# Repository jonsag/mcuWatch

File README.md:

# mcuWatch

A watch based on an ATmega32P or an ESP8266 module with an RTC clock and a TFT screen  

## Links

### Arduino

[Tutorial on how to use DS3231 RTC Module](https://create.arduino.cc/projecthub/mdraber/tutorial-on-how-to-use-ds3231-rtc-module-e12b38)  
[The ST7735 TFT with arduino](https://www.electronics-lab.com/project/using-st7735-1-8-color-tft-display-arduino/)  
[Arduino DS3231 Real Time Clock With Color TFT](https://www.instructables.com/Arduino-DS3231-Real-time-clock-with-color-TFT/)  

### ESP8266

[ESP8266 pinout reference and how to use GPIO pins](https://microcontrollerslab.com/esp8266-pinout-reference-gpio-pins/)  
[ESP8266 Pinout Reference: Which GPIO pins should you use?](https://randomnerdtutorials.com/esp8266-pinout-reference-gpios/)  
[NodeMCU GPIO with Arduino IDE](https://www.electronicwings.com/nodemcu/nodemcu-gpio-with-arduino-ide)  

[Connecting a 1.77 inch TFT LCD screen to ESP8266](http://gogs.info/blog/2020/03/connecting-177-inch-TFT-LCD-screen-ESP8266/)  
[NodeMCU and 1.8" SPI ST7735 Display](https://www.instructables.com/NodeMCU-and-18-SPI-ST7735-Display/)  
[Interfacing ESP8266 NodeMCU with ST7735 TFT](https://simple-circuit.com/esp8266-nodemcu-st7735s-tft/)  
[ESP8266 NodeMCU Internet Clock with ST7735 TFT](https://simple-circuit.com/esp8266-nodemcu-st7735-tft-internet-clock/)  

### Libraries

[DS3231](https://github.com/NorthernWidget/DS3231)  
[Adafruit GFX Library](https://github.com/adafruit/Adafruit-GFX-Library)  
[Adafruit SSD1306](https://github.com/adafruit/Adafruit_SSD1306)  

#### Tiny/Compact TFT Graphics Library

[Tiny TFT Graphics Library](http://www.technoblogy.com/show?L6I)  

[Compact TFT Graphics Library](http://www.technoblogy.com/show?2LMJ)
[Source](https://github.com/technoblogy/compact-tft-graphics-library)

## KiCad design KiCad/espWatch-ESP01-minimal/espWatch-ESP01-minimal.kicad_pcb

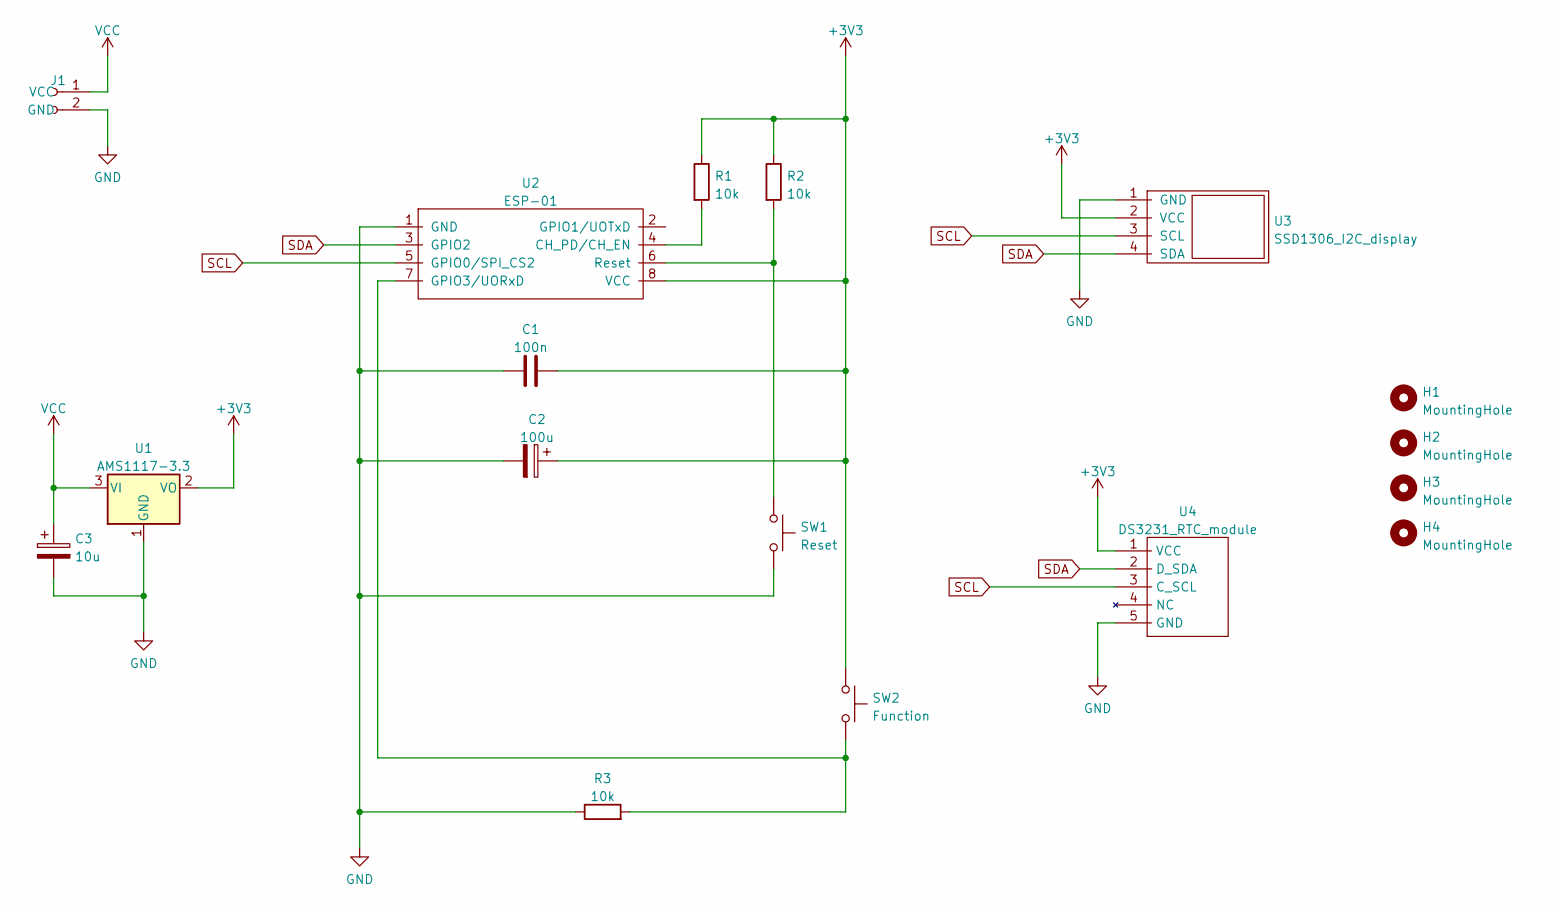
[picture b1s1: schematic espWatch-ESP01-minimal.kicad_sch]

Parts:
C1: 100n; C_Disc_D3.0mm_W1.6mm_P2.50mm_larg
C2: 100u; CP_Radial_D5.0mm_P2.00mm_larger
C3: 10u; CP_Radial_D5.0mm_P2.00mm_larger
H1, H2, H3, H4: MountingHole; MountingHole_3.2mm_M3
J1: 2-pin_power_input_header; 2-pin_power_input_header_larger_pads
R1, R2, R3: 10k; R_Axial_DIN0207_L6.3mm_D2.5mm_P10.16mm_Horizontal_larger_pa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
SW1: Reset; SW_PUSH_6mm_large
SW2: Function; SW_PUSH_6mm_large
U1: AMS1117-3.3; SOT-223-3_TabPin2
U2: ESP-01; ESP-01_w_pin_socket_large
U3: SSD1306_I2C_display; SSD1306_I2C_0.96_OLED_display_large
U4: DS3231_RTC_module; DS3231_RTC_module_large

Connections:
+3V3: C1.2, C2.1, R1.1, R2.1, SW2.1, U1.2 (VO), U2.8 (VCC), U3.2 (VCC), U4.1 (VCC)
GND: C1.1, C2.2, C3.2, J1.2 (GND), R3.1, SW1.2, U1.1 (GND), U2.1 (GND), U3.1 (GND), U4.5 (GND)
unnamed: R1.2, U2.4 (CH_PD/CH_EN)
unnamed: R2.2, SW1.1, U2.6 (Reset)
unnamed: R3.2, SW2.2, U2.7 (GPIO3/UORxD)
SCL: U2.5 (GPIO0/SPI_CS2), U3.3 (SCL), U4.3 (C_SCL)
SDA: U2.3 (GPIO2), U3.4 (SDA), U4.2 (D_SDA)
VCC: C3.1, J1.1 (VCC), U1.3 (VI)

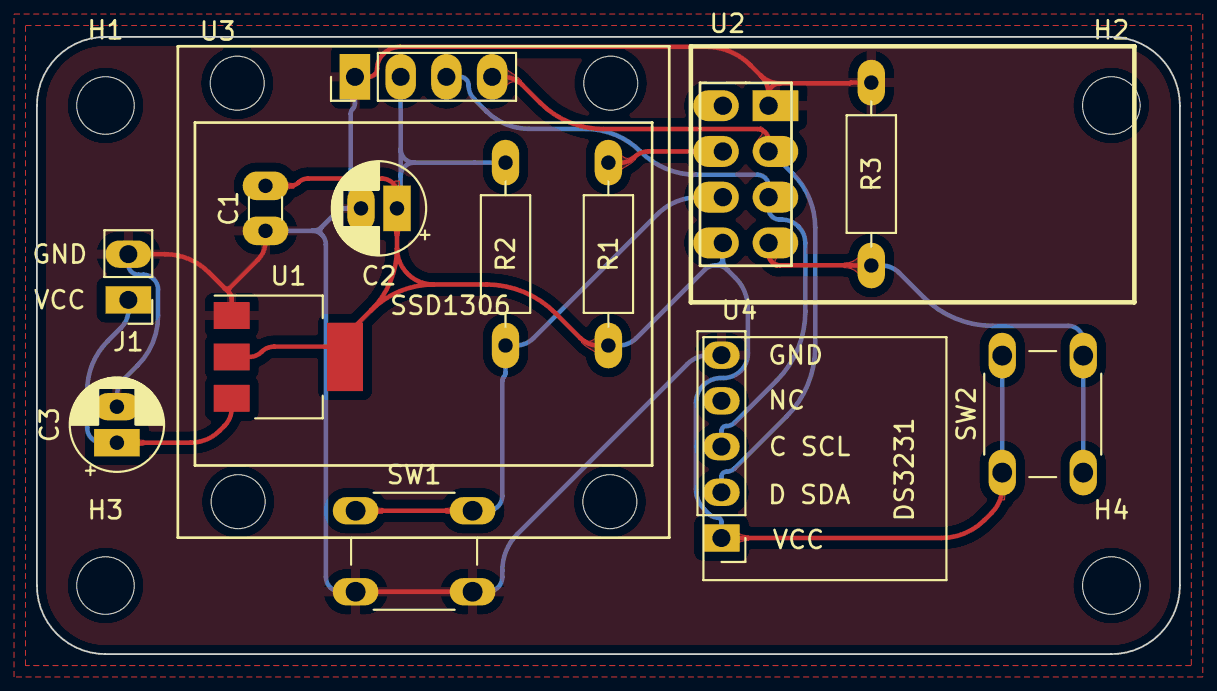
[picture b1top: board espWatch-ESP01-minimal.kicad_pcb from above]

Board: 2 copper layers, 63.5 x 34.3 mm, 17 parts (0 on the bottom side), 8 nets.

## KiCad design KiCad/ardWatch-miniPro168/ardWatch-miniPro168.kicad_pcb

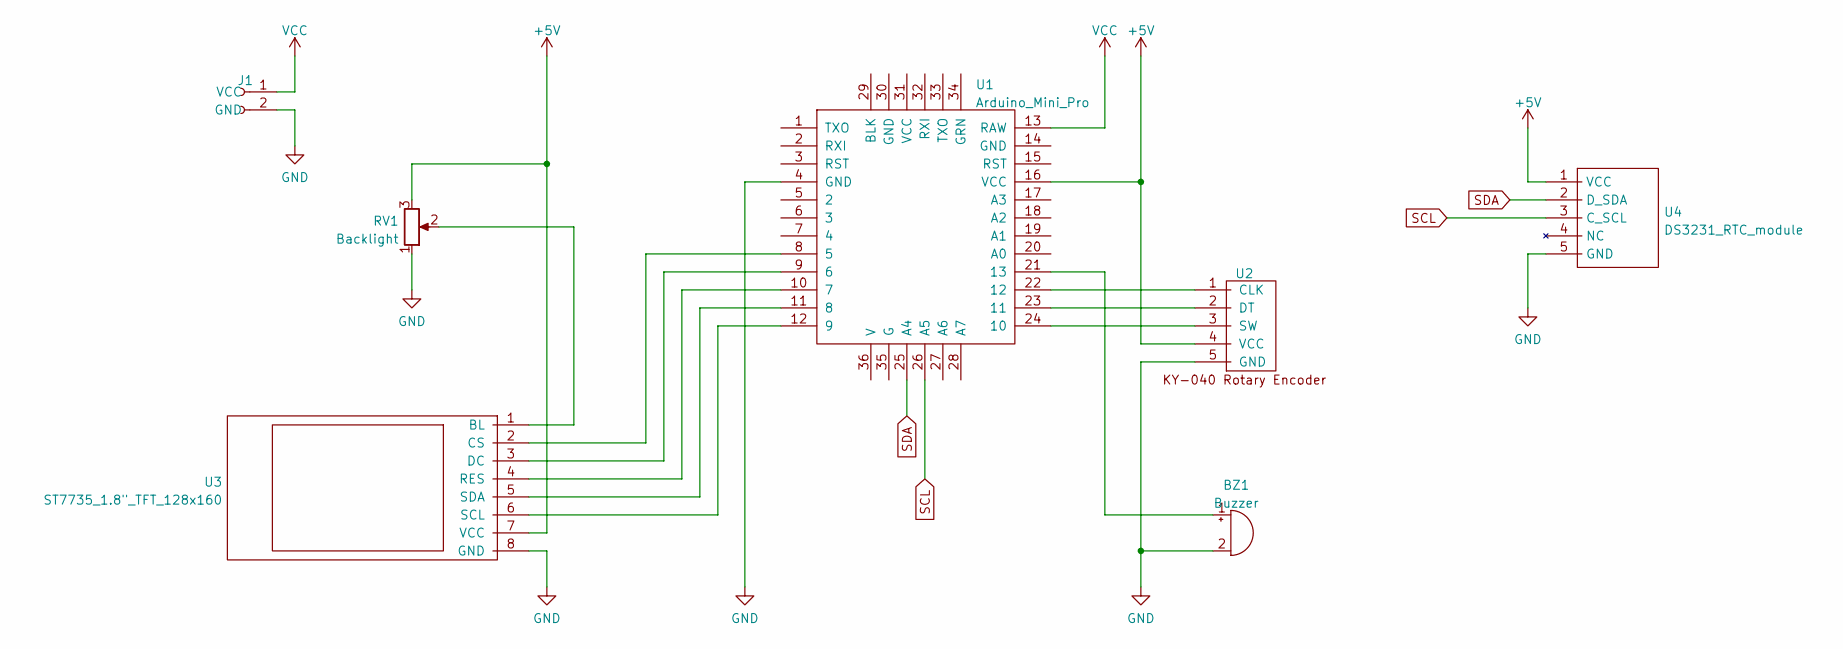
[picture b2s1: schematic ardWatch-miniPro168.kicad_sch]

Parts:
BZ1: Buzzer; Buzzer_TDK_PS1240P02BT_D12.2mm_H6.5mm_large
J1: 2-pin_power_input_header; 2-pin_power_input_header_larger_pads
RV1: Backlight; Potentiometer_Bourns_3339P_Vertical_large
U1: Arduino_Mini_Pro; Arduino_Pro_Mini_vC_larger_pads
U2: KY-040_Rotary_Encoder; KY-040_rotary_encoder module_w_header_large
U3: ST7735_1.8"_TFT_128x160; ST7735_1.8_TFT_display_128x160_large
U4: DS3231_RTC_module; DS3231_RTC_module_large

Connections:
+5V: RV1.3, U1.16 (VCC), U2.4 (VCC), U3.7 (VCC), U4.1 (VCC)
GND: BZ1.2 (+), J1.2 (GND), RV1.1, U1.4 (GND), U2.5 (GND), U3.8 (GND), U4.5 (GND)
unnamed: U1.8 (5), U3.2 (CS)
unnamed: U1.9 (6), U3.3 (DC)
unnamed: U1.10 (7), U3.4 (RES)
unnamed: U1.11 (8), U3.5 (SDA)
unnamed: U1.12 (9), U3.6 (SCL)
unnamed: BZ1.1 (-), U1.21 (13)
unnamed: U1.22 (12), U2.1 (CLK)
unnamed: U1.23 (11), U2.2 (DT)
unnamed: U1.24 (10), U2.3 (SW)
unnamed: RV1.2, U3.1 (BL)
SCL: U1.26 (A5), U4.3 (C_SCL)
SDA: U1.25 (A4), U4.2 (D_SDA)
VCC: J1.1 (VCC), U1.13 (RAW)

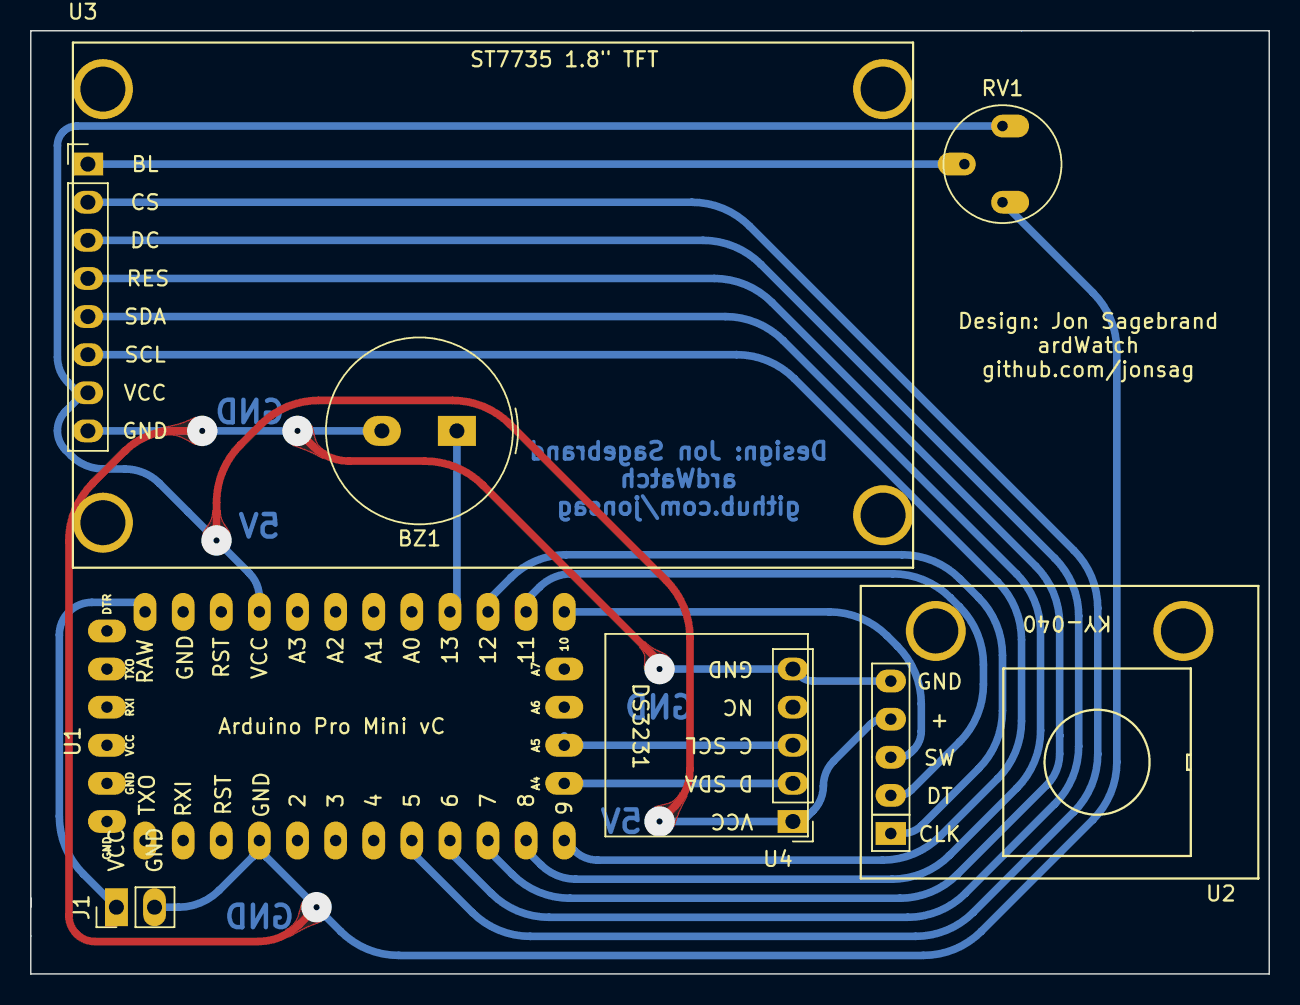
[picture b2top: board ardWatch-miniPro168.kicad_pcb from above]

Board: 2 copper layers, 82.5 x 62.9 mm, 7 parts (0 on the bottom side), 15 nets.

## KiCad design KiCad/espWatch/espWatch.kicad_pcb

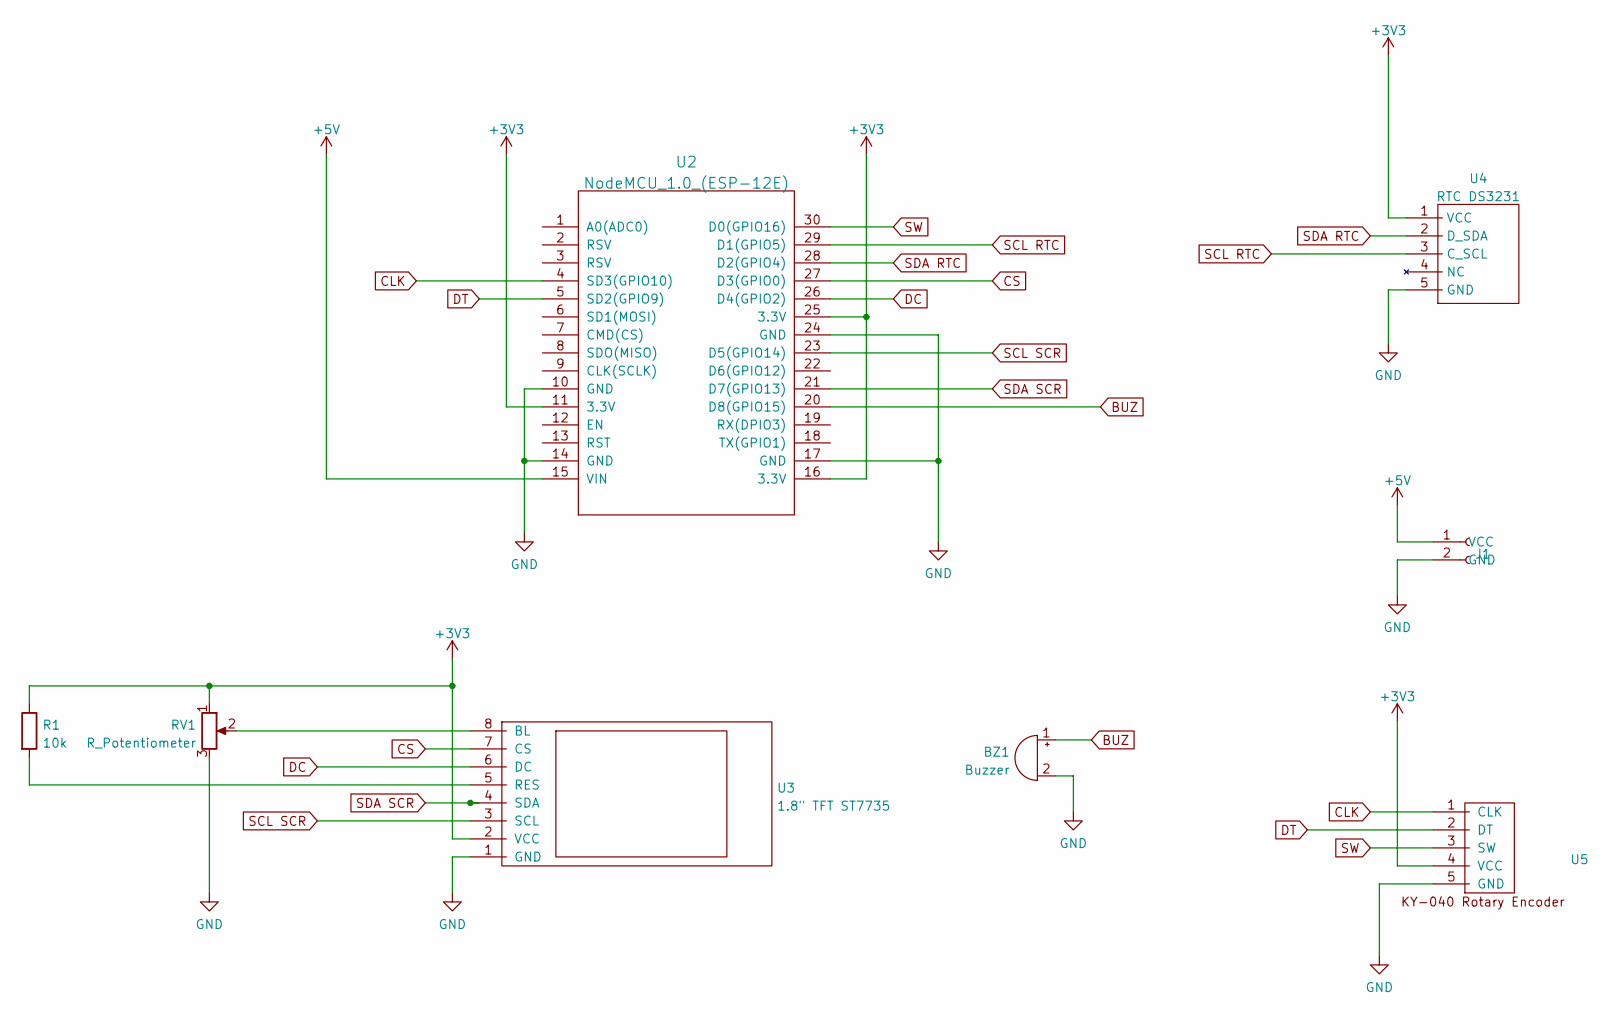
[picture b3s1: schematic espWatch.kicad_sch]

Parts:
BZ1: Buzzer; Buzzer_TDK_PS1240P02BT_D12.2mm_H6.5mm_large
J1: 2-pin_power_input_header; 2-pin_power_input_header_larger_pads
R1: 10k; R_Axial_DIN0207_L6.3mm_D2.5mm_P10.16mm_Horizontal_larger_pa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
RV1: R_Potentiometer; Potentiometer_Bourns_3339P_Vertical_large
U2: NodeMCU_1.0_(ESP-12E); NodeMCU-LoLinV3_w_pinsockets_large
U3: 1.8" TFT ST7735; ST7735_1.8_TFT_display_128x160_large
U4: RTC DS3231; DS3231_RTC_module_large
U5: KY-040_Rotary_Encoder; KY-040_rotary_encoder module_w_header_large

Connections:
+3V3: R1.1, RV1.1, U2.11 (3.3V), U2.16 (3.3V), U2.25 (3.3V), U3.2 (VCC), U4.1 (VCC), U5.4 (VCC)
+5V: J1.1 (VCC), U2.15 (VIN)
BUZ: BZ1.1 (-), U2.20 (D8(GPIO15))
CLK: U2.4 (SD3(GPIO10)), U5.1 (CLK)
CS: U2.27 (D3(GPIO0)), U3.7 (CS)
DC: U2.26 (D4(GPIO2)), U3.6 (DC)
DT: U2.5 (SD2(GPIO9)), U5.2 (DT)
GND: BZ1.2 (+), J1.2 (GND), RV1.3, U2.10 (GND), U2.14 (GND), U2.17 (GND), U2.24 (GND), U3.1 (GND), U4.5 (GND), U5.5 (GND)
unnamed: R1.2, U3.5 (RES)
unnamed: RV1.2, U3.8 (BL)
SCL RTC: U2.29 (D1(GPIO5)), U4.3 (C_SCL)
SCL SCR: U2.23 (D5(GPIO14)), U3.3 (SCL)
SDA RTC: U2.28 (D2(GPIO4)), U4.2 (D_SDA)
SDA SCR: U2.21 (D7(GPIO13)), U3.4 (SDA)
SW: U2.30 (D0(GPIO16)), U5.3 (SW)

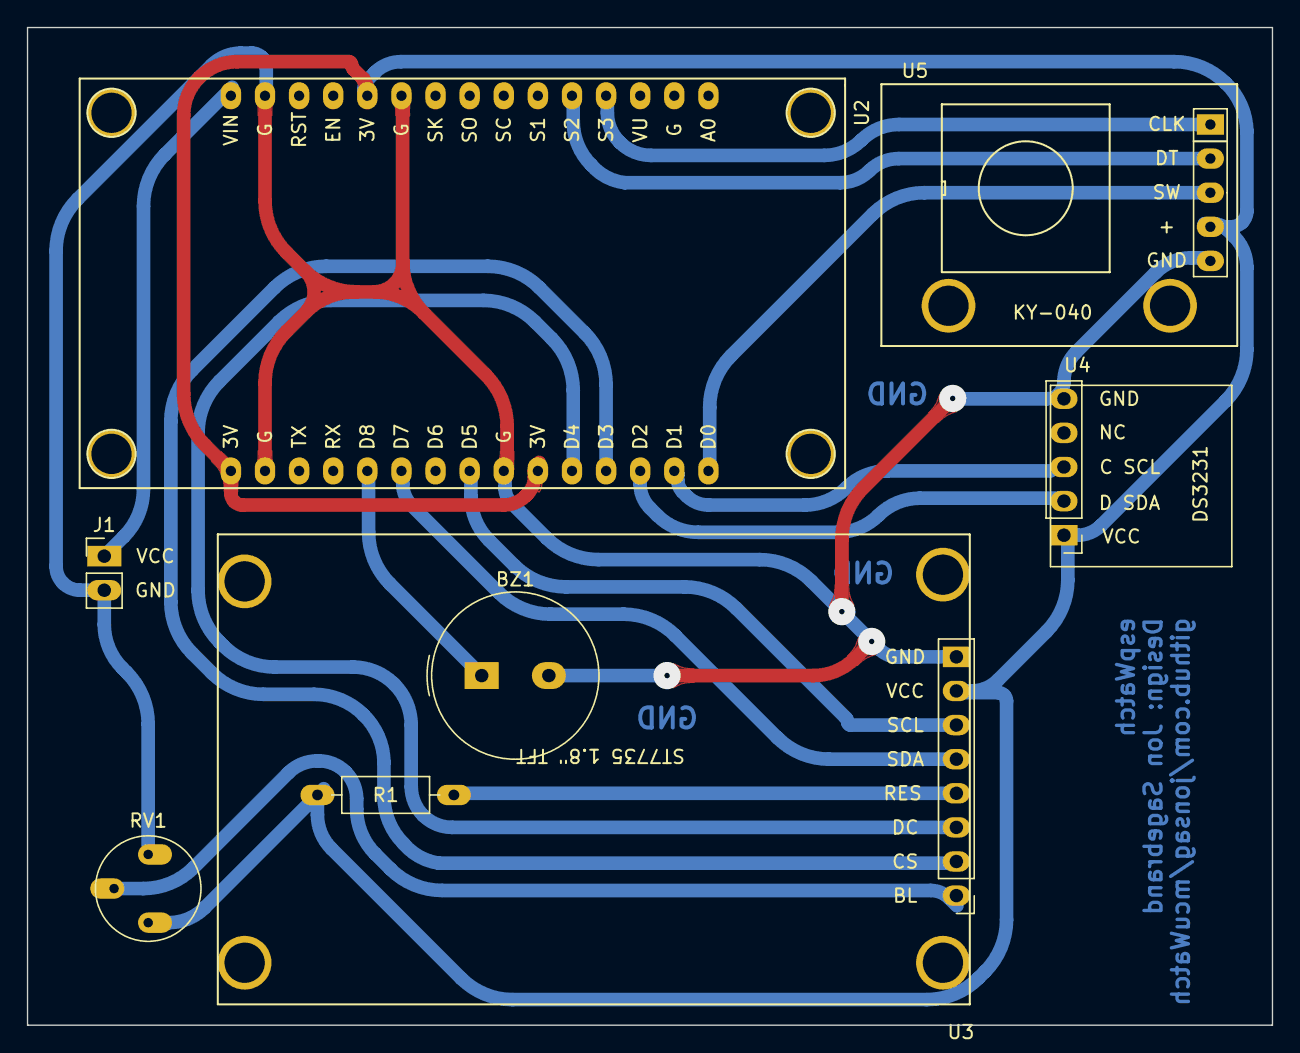
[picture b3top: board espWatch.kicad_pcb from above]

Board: 2 copper layers, 92.7 x 74.3 mm, 8 parts (0 on the bottom side), 15 nets.

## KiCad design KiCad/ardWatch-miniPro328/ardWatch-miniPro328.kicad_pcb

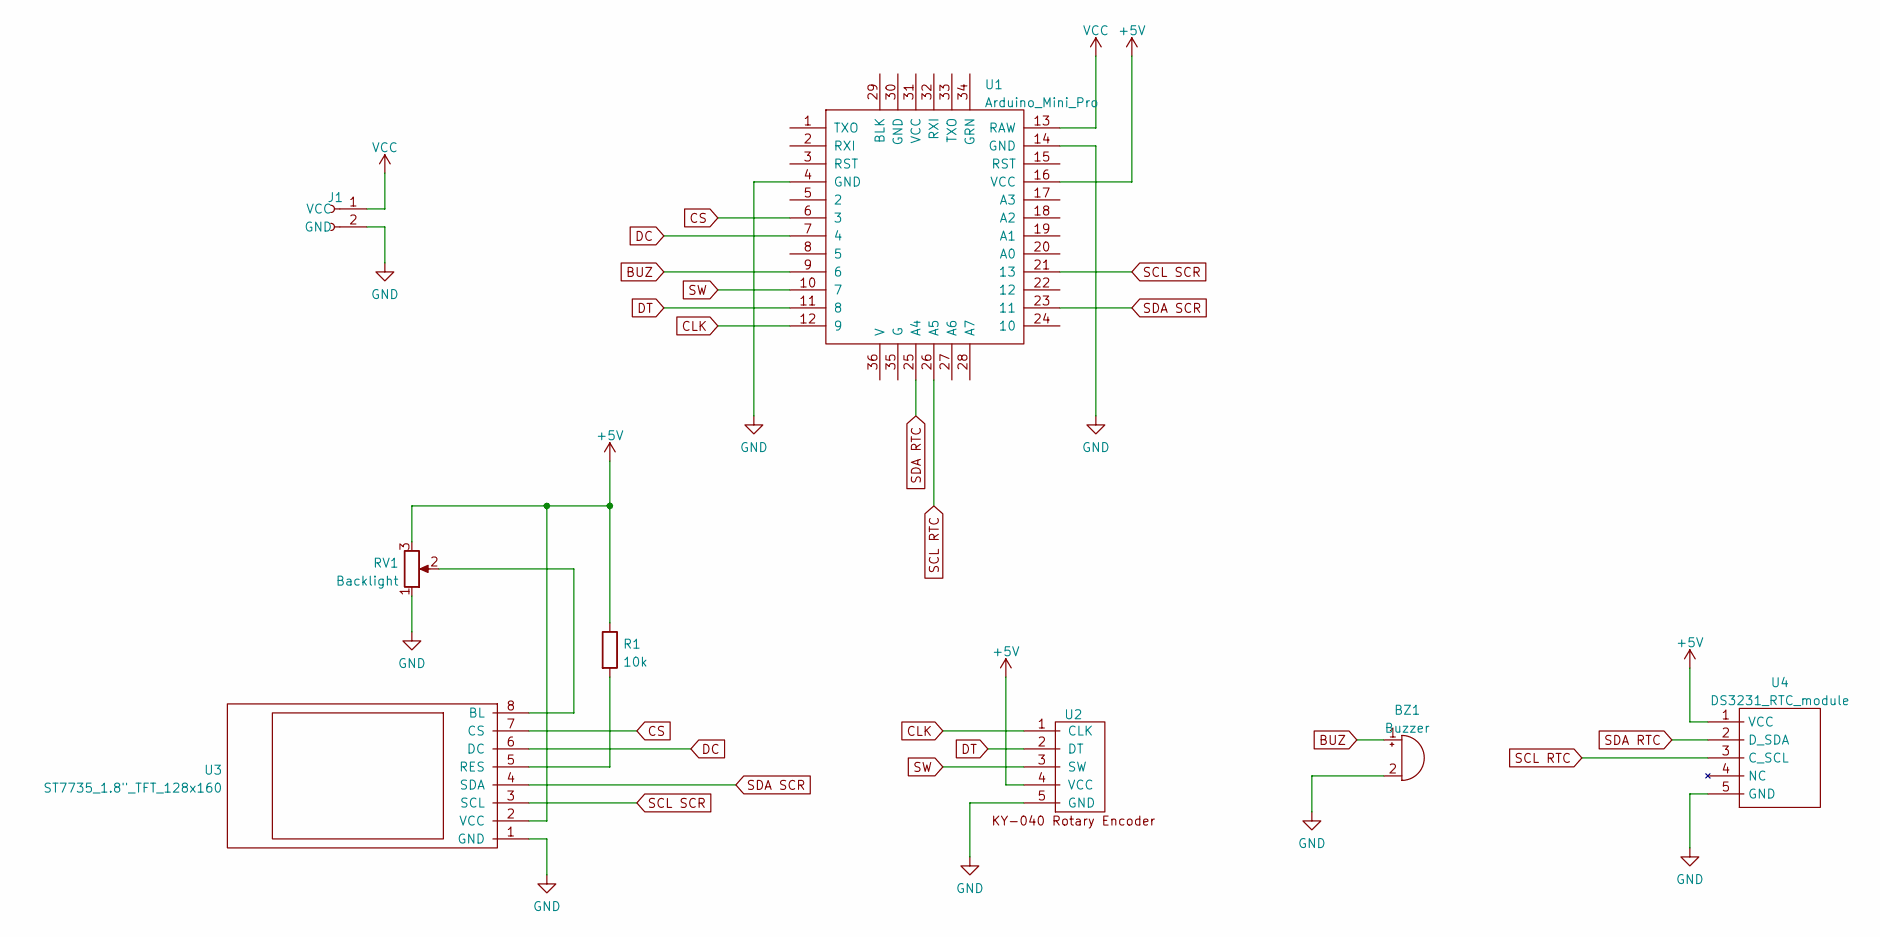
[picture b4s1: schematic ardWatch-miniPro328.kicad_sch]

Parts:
BZ1: Buzzer; Buzzer_TDK_PS1240P02BT_D12.2mm_H6.5mm_large
J1: 2-pin_power_input_header
R1: 10k; R_Axial_DIN0207_L6.3mm_D2.5mm_P10.16mm_Horizontal_larger_pa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
RV1: Backlight; Potentiometer_Bourns_3339P_Vertical_large
U1: Arduino_Mini_Pro; Arduino_Pro_Mini_vA_sides_n_A4,A5_large
U2: KY-040_Rotary_Encoder; KY-040_rotary_encoder module_w_header_large
U3: ST7735_1.8"_TFT_128x160; ST7735_1.8_TFT_display_128x160_large
U4: DS3231_RTC_module; DS3231_RTC_module_large

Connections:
+5V: R1.1, RV1.3, U1.16 (VCC), U2.4 (VCC), U3.2 (VCC), U4.1 (VCC)
BUZ: BZ1.1 (-), U1.9 (6)
CLK: U1.12 (9), U2.1 (CLK)
CS: U1.6 (3), U3.7 (CS)
DC: U1.7 (4), U3.6 (DC)
DT: U1.11 (8), U2.2 (DT)
GND: BZ1.2 (+), J1.2 (GND), RV1.1, U1.4 (GND), U1.14 (GND), U2.5 (GND), U3.1 (GND), U4.5 (GND)
unnamed: R1.2, U3.5 (RES)
unnamed: RV1.2, U3.8 (BL)
SCL RTC: U1.26 (A5), U4.3 (C_SCL)
SCL SCR: U1.21 (13), U3.3 (SCL)
SDA RTC: U1.25 (A4), U4.2 (D_SDA)
SDA SCR: U1.23 (11), U3.4 (SDA)
SW: U1.10 (7), U2.3 (SW)
VCC: J1.1 (VCC), U1.13 (RAW)

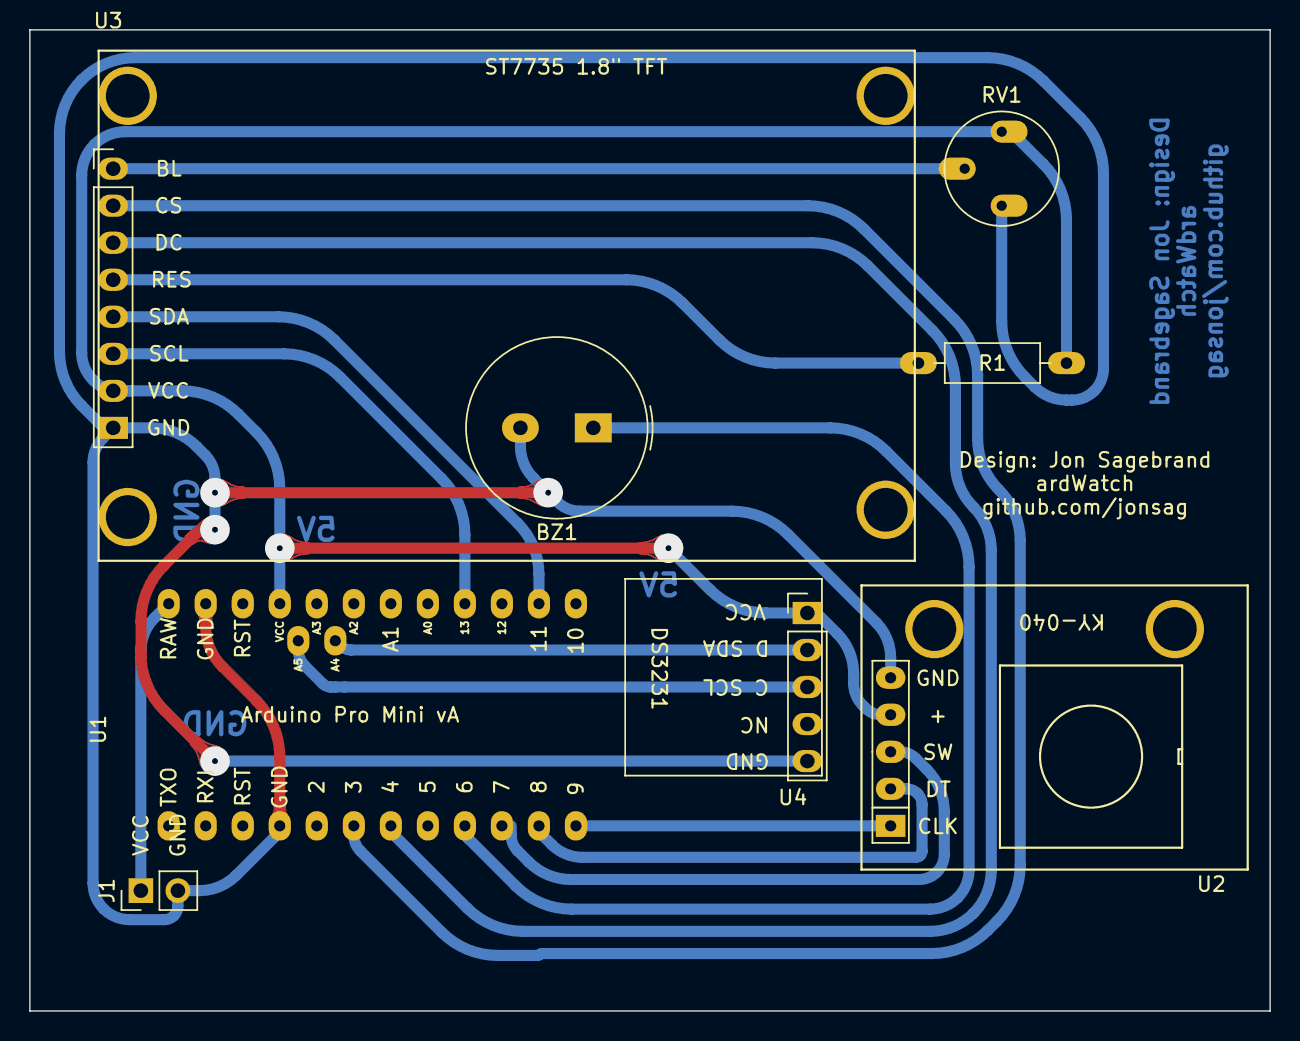
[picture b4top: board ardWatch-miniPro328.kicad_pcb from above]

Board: 2 copper layers, 85.1 x 67.3 mm, 8 parts (0 on the bottom side), 15 nets.

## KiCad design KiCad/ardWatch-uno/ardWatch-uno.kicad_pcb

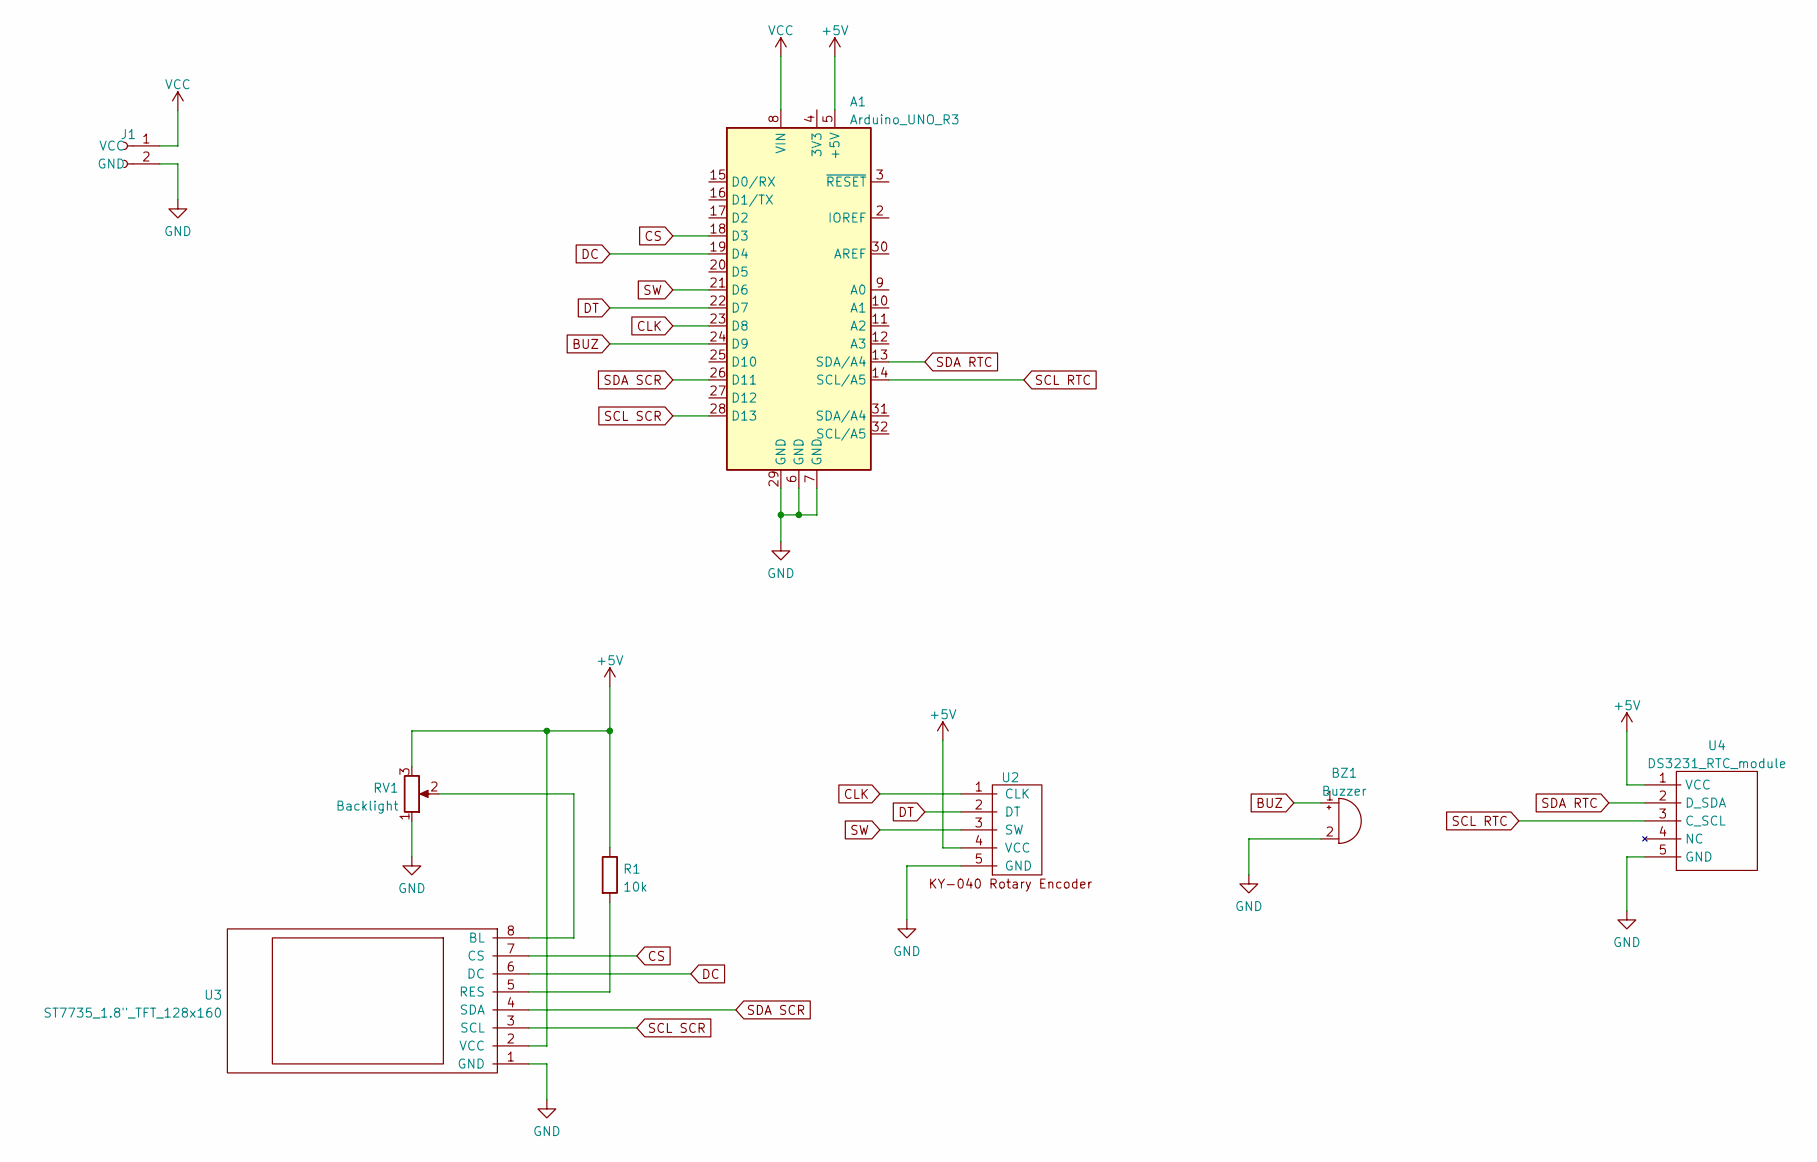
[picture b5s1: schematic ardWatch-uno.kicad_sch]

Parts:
A1: Arduino_UNO_R3; Arduino_UNO_R3_shield_large
BZ1: Buzzer; Buzzer_TDK_PS1240P02BT_D12.2mm_H6.5mm_large
J1: 2-pin_power_input_header
R1: 10k; R_Axial_DIN0207_L6.3mm_D2.5mm_P10.16mm_Horizontal_larger_pa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
RV1: Backlight; Potentiometer_Bourns_3339P_Vertical_large
U2: KY-040_Rotary_Encoder; KY-040_rotary_encoder module_w_header_large
U3: ST7735_1.8"_TFT_128x160; ST7735_1.8_TFT_display_128x160_large
U4: DS3231_RTC_module; DS3231_RTC_module_large

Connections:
+5V: A1.5 (+5V), R1.1, RV1.3, U2.4 (VCC), U3.2 (VCC), U4.1 (VCC)
BUZ: A1.24 (D9), BZ1.1 (-)
CLK: A1.23 (D8), U2.1 (CLK)
CS: A1.18 (D3), U3.7 (CS)
DC: A1.19 (D4), U3.6 (DC)
DT: A1.22 (D7), U2.2 (DT)
GND: A1.6 (GND), A1.7 (GND), A1.29 (GND), BZ1.2 (+), J1.2 (GND), RV1.1, U2.5 (GND), U3.1 (GND), U4.5 (GND)
unnamed: R1.2, U3.5 (RES)
unnamed: RV1.2, U3.8 (BL)
SCL RTC: A1.14 (SCL/A5), U4.3 (C_SCL)
SCL SCR: A1.28 (D13), U3.3 (SCL)
SDA RTC: A1.13 (SDA/A4), U4.2 (D_SDA)
SDA SCR: A1.26 (D11), U3.4 (SDA)
SW: A1.21 (D6), U2.3 (SW)
VCC: A1.8 (VIN), J1.1 (VCC)

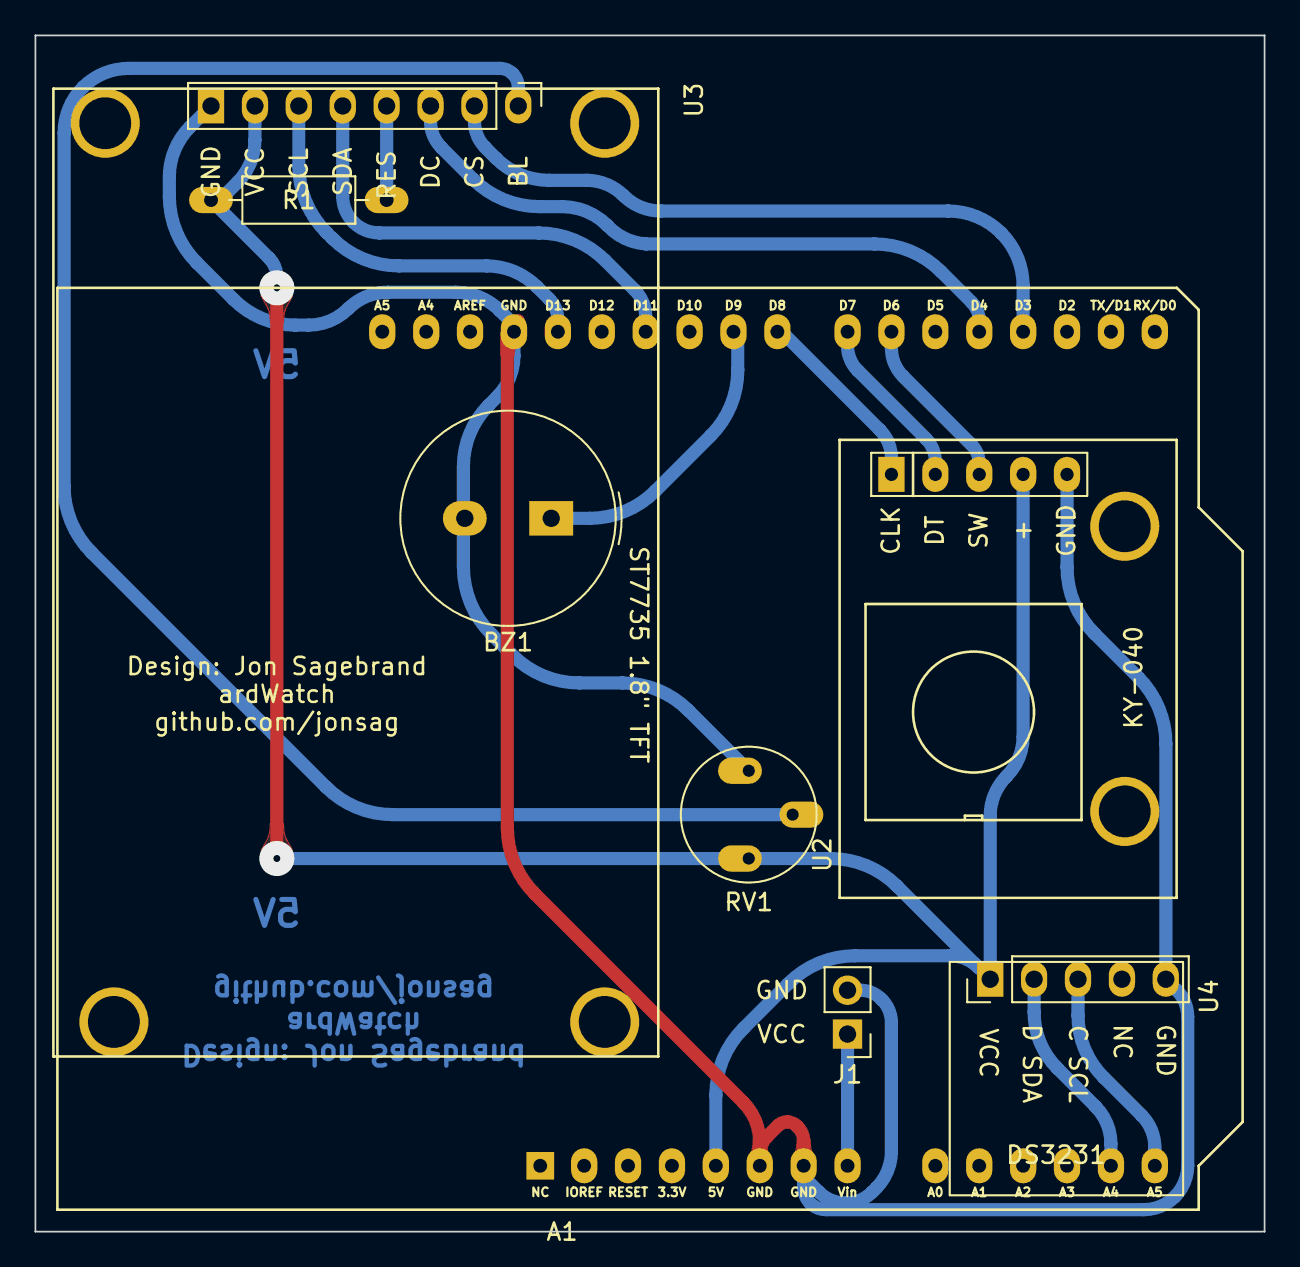
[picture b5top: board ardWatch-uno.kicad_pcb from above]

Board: 2 copper layers, 71.1 x 69.2 mm, 8 parts (0 on the bottom side), 15 nets.

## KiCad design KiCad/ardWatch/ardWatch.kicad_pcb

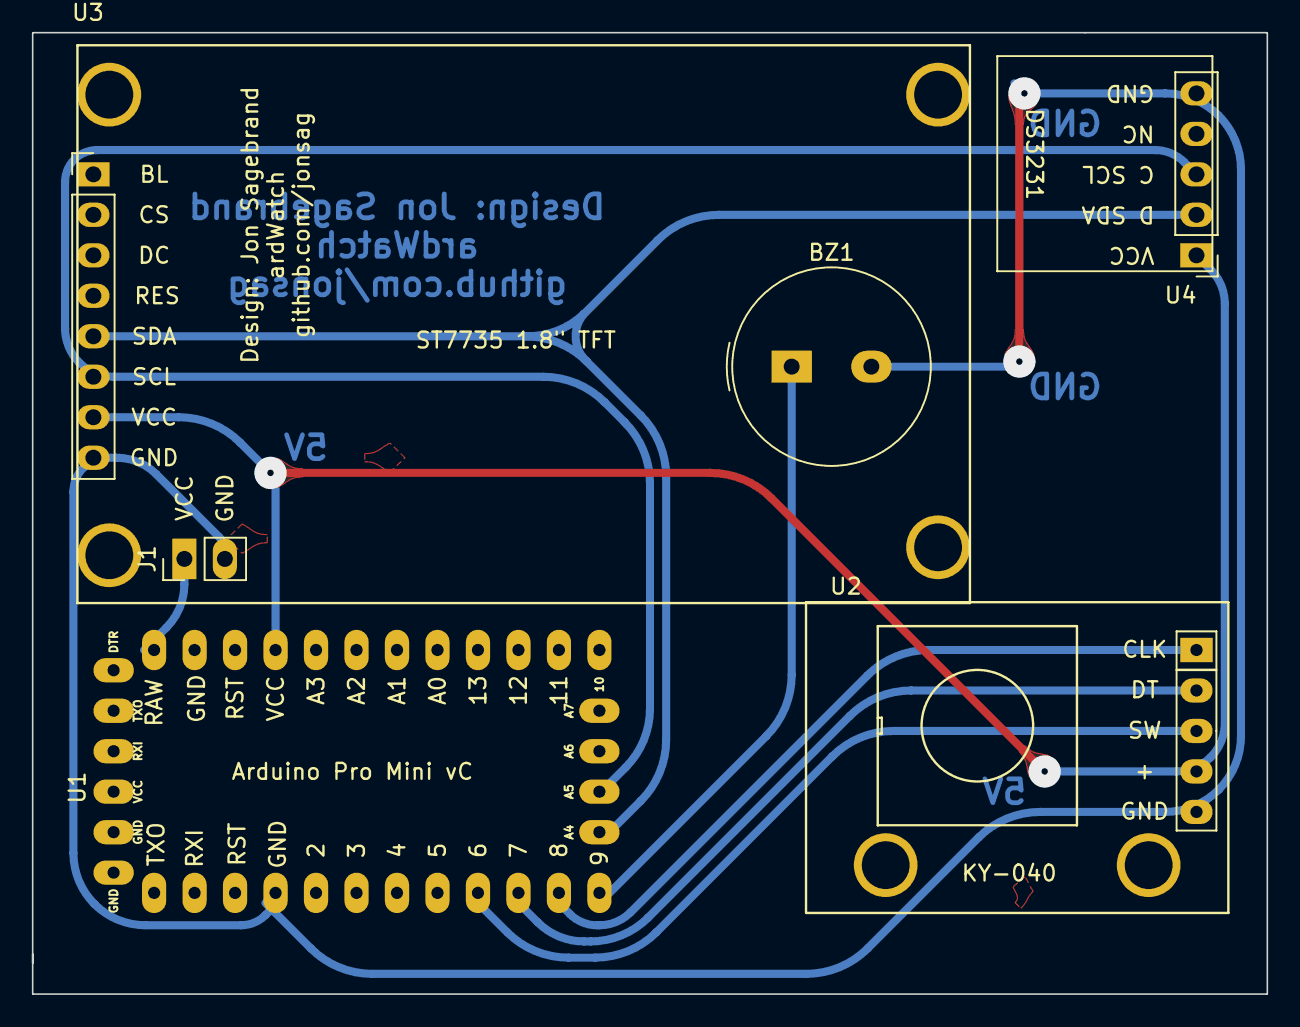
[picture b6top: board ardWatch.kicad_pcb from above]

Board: 2 copper layers, 77.5 x 60.3 mm, 6 parts (0 on the bottom side), 9 nets.

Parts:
BZ1: Buzzer; Buzzer_TDK_PS1240P02BT_D12.2mm_H6.5mm_large
J1: 2-pin_power_input_header; 2-pin_power_input_header_larger_pads
U1: Arduino_Mini_Pro; Arduino_Pro_Mini_vC_larger_pads
U2: KY-040_Rotary_Encoder; KY-040_rotary_encoder module_w_header_large
U3: ST7735_1.8"_TFT_128x160; ST7735_1.8_TFT_display_128x160_large
U4: DS3231_RTC_module; DS3231_RTC_module_large

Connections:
+5V: U1.16 (VCC), U2.4 (VCC), U3.7 (VCC), U4.1 (VCC)
GND: BZ1.2 (+), J1.2 (GND), U1.4 (GND), U2.5 (GND), U3.8 (GND), U4.5 (GND)
unnamed: BZ1.1 (-), U1.12 (9)
unnamed: U1.11 (8), U2.1 (CLK)
unnamed: U1.10 (7), U2.2 (DT)
unnamed: U1.9 (6), U2.3 (SW)
SCL: U1.26 (A5), U3.6 (SCL), U4.3 (C_SCL)
SDA: U1.25 (A4), U3.5 (SDA), U4.2 (D_SDA)
VCC: J1.1 (VCC), U1.13 (RAW)

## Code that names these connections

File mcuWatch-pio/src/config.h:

#include <Wire.h>

/**********
 * Debug
 **********/
#define DEBUG 0 // debugMess is off when 0
#define INFO 1

#if DEBUG
#define debugMess(x) Serial.print(x)
#define debugMessln(x) Serial.println(x)

#else
#define debugMess(x)
#define debugMessln(x)
#endif

#if INFO || DEBUG
#define infoMess(x) Serial.print(x)
#define infoMessln(x) Serial.println(x)
#else
#define infoMess(x)
#define infoMessln(x)
#endif

/*
SPI (ST7735)
Function    Screen pin  Mini        Uno         Mega        ESP8266     ESP-01      Comment
-----       -----       -----       -----       -----       -----       -----       -----
SCK         3           D13*)       D13*)       D52*)       D5/GPIO14*)             SCL, HSCLK, SPI Clock, Hardware SPI clk
SDA         4           D11*)       D11*)       D51*)       D7/GPIO13*)             SPI Data, MOSI, HMOSI, data to screen
RES         5           D5          D5          D5          D6/GPIO12               RST, MISO, HMISO, screen reset
DC          6           D4          D4          D4          D4/GPIO2                Register Select, labelled as DC in Adafruit code
CS          7           D3          D3          D3          D3/GPIO0                Chip Select, defined as Slave Select in SPI

I2C (RTC and SSD1306)
Function    RTC         Screen      Uno, Mini   Mega        ESP8266     ESP-01
-----       -----       -----       -----       -----       -----       -----
Address     0x68        0x3C
SDA         2                       A4*)         20*)      D2/GPIO4*)  3/GPIO2
SCL         3                       A5*)         21*)      D1/GPIO5*)  5/GPIO0
  oldNow = now;

Rotary encoder
Function                Arduino 168 Arduino 328 ESP8266     ESP-01
-----                   -----       -----       -----       -----
CLK                                 D9
DT                                  D8
SW                                  D7

Buzzer
Function                Arduino 168 Arduino 328 ESP8266     ESP-01
-----                   -----       -----       -----       -----
+                                   D6          D8/GPIO15

*) Must be these pins as they are set in firmware/hardware

Find macro definitions:
$ grep board= `find ~/.platformio/ -name boards.txt` | cut -f2 -d= | sort -u
*/

/**********
 * Pins
 **********/
// #define i2cSDA D2
// #define i2cSCK D1

#define tftSCK D5
#define tftSDA D7

#define tftRES D6
#define tftDC D4 // GPIO2, TFT display SPI chip select pin
#define tftCS D3 // GPIO0, TFT display data/command select pin

#define rotCLK SD3 // GPIO10
#define rotDT SD2  // GPIO9
#define rotSW D0   // GPIO16

#define buz D8 // GPIO2

/**********
 * TFT screen
 **********/
#include <Adafruit_GFX.h>
#include <Adafruit_ST7735.h>

Adafruit_ST7735 myScreen = Adafruit_ST7735(tftCS, tftDC, tftRES);

// colours
#define bgCol ST77XX_BLACK

#define helpLineCol ST77XX_GREEN

#

/*
#define colBla ST77XX_BLACK   // 0x0000
#define colWhi ST77XX_WHITE   // 0xFFFF
#define colRed ST77XX_RED     // 0xF800
#define colGre ST77XX_GREEN   // 0x07E0
#define colBlu ST77XX_BLUE    // 0x001F
#define colCya ST77XX_CYAN    // 0x07FF
#define colMag ST77XX_MAGENTA // 0xF81F
#define colYel ST77XX_YELLOW  // 0xFFE0
#define colOra ST77XX_ORANGE  // 0xFC00
*/

// sizes
#define startCol ST77XX_WHITE
#define startSize 1

// positions
#define XSplits 4 // split screen vertically, this is used below for positions
#define YSplits 8 // split screen horizontally, this is used below for positions

#define dateCol ST77XX_YELLOW
#define dateSize 1
#define dateXPos 2
#define dateYPos 1

#define timeCol ST77XX_GREEN
#define timeSize 4
#define timeNowXPos 2
#define timeNowYPos 2

#define tempCol ST77XX_YELLOW
#define tempNowSize 3
#define tempNowXPos 2
#define tempNowYPos 4

#define tempSize 2

#define maxTempCol ST77XX_RED
#define tempMaxXPos 3
#define tempMaxYPos 6

#define minTempCol ST77XX_BLUE
#define tempMinXPos 1
#define tempMinYPos 6

#define wifiStatusSize 1
#define wifiStatusOKCol ST77XX_GREEN
#define wifiStatusDownCol ST77XX_RED
#define wifiStatusXPos 1
#define wifiStatusYPos 0
const String wifiStatusString = "WiFi";

#define driftSize 1
#define driftCol ST77XX_GREEN
#define driftXPos 3
#define driftYPos 0

// compensations
#define timeXOffs 2

// font, how many pixels are the font built of
#define pixX 6
#define pixY 8

/**********
 * RTC
 **********/
/*
RTC module from above
------------
| 5 GND     |
| 4 NC      |
| 3 C SCL   |
| 2 D SDA   |
| 1 VCC     |
------------
*/

#include <Sodaq_DS3231.h>

const int hourOffs = 0;

DateTime now;
DateTime oldNow;
DateTime oldEpoch;

float temperature;
float oldTemp;

float maxTemp = -100.0;
float minTemp = 100.0;

DateTime maxTempNow;
DateTime minTempNow;

byte year;
byte month;
byte date;
byte dOW;
byte hour;
byte minute;
byte second;

const char *monthName[12] = {
    "Jan", "Feb", "Mar", "Apr", "May", "Jun",
    "Jul", "Aug", "Sep", "Oct", "Nov", "Dec"};

const char *dayName[7] = {
    "Mon", "Tue", "Wed", "Thu", "Fri", "Sat", "Sun"};

long lastRTCCheckMillis;
const int RTCCheckInterval = 5000;

/**********
 * Wifi
 **********/
#include <ESP8266WiFi.h>
#include <WiFiClient.h>

#include "secrets.h"

const char *ssid = STASSID;
const char *password = STAPSK;

/**********
 * Web server
 **********/
#include <ESP8266WebServer.h>
#include <ESP8266mDNS.h>

ESP8266WebServer server(80);

#define wifiTimeout 10000

long startTime;
boolean connected = false;

/**********
 * NTP
 **********/
#include <NTPClient.h>
#include <WiFiUdp.h>

#include <time.h>      // for time() ctime() ...
#include <coredecls.h> // optional settimeofday_cb() callback to check on server

#define MY_NTP_SERVER "se.pool.ntp.org" // find best pool at https://www.ntppool.org

// choose time zone from list at https://github.com/nayarsystems/posix_tz_db/blob/master/zones.csv
#define MY_TZ "CET-1CEST,M3.5.0,M10.5.0/3" // Europe/Stockholm

#define timeOffset 7200 // time offset in seconds

WiFiUDP ntpUDP;
NTPClient timeClient(ntpUDP, MY_NTP_SERVER);

long lastNTPCheckMillis;
#define NTPCheckInterval 60000

/**********
 * EEPROM
 **********/
#include <EEPROM.h>

#define EEPROM_SIZE 512 // esp8266 has 512 bytes of eeprom
#define dtNtpAddress 0  // time when RTC was set from NTP (4 bytes)

DateTime dtNTP;

#define maxDrift 10

/**********
 * Rotary encoder
 **********/

/**********
 * Buzzer
 **********/

/**********
 * Misc
 **********/
long currentMillis;

#define serialSpeed 9600
#define serialTimeout 10000
